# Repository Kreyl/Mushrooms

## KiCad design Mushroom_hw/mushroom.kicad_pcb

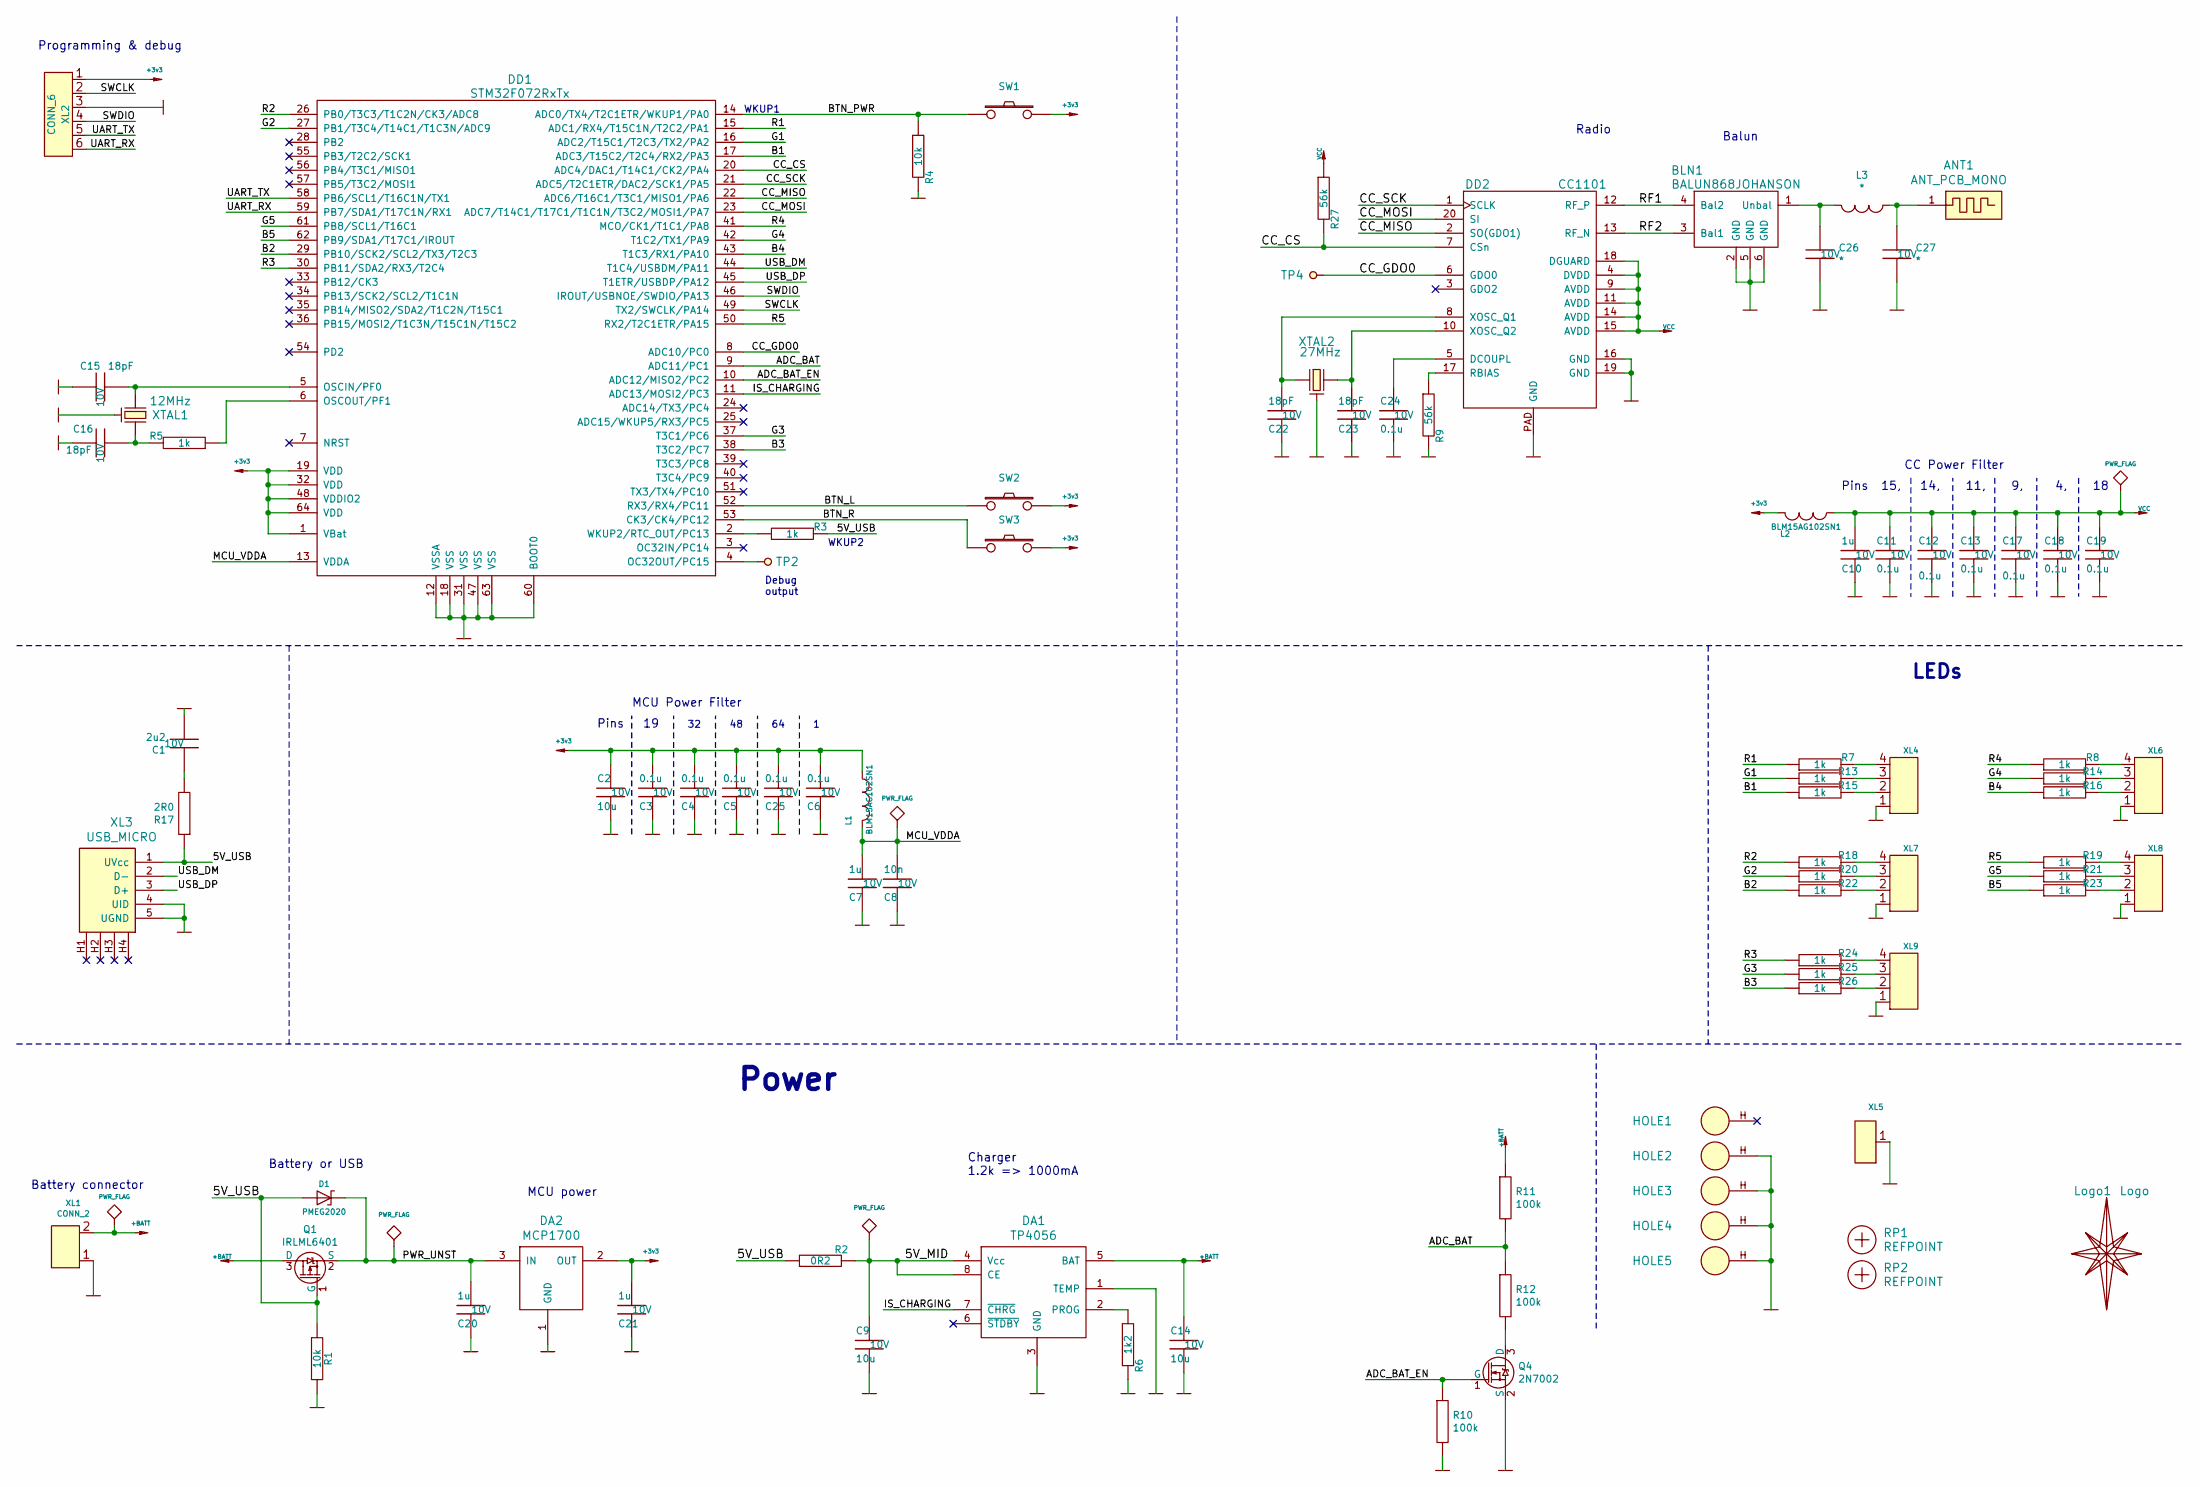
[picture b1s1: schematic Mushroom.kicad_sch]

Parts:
ANT1: ANT_PCB_MONO; Firefly_868
BLN1: BALUN868JOHANSON; BALUN_JOHANSON868
C1: 2u2; CAP_0603_Silks; Tolerance 20%; Voltage 10V
C2, C9, C14: 10u; CAP_0603_Silks; Tolerance 20%; Voltage 10V
C3, C4, C5, C6, C11, C12, C13, C17, C18, C19, C24, C25: 0.1u; CAP_0603_Silks; Tolerance 20%; Voltage 10V
C7, C10, C20, C21: 1u; CAP_0603_Silks; Tolerance 20%; Voltage 10V
C8: 10n; CAP_0603_Silks; Tolerance 20%; Voltage 10V
C15, C16, C22, C23: 18pF; CAP_0603_Silks; Tolerance 20%; Voltage 10V
C26, C27: *; CAP_0402; Tolerance 20%; Voltage 10V
D1: PMEG2020; SOD323
DA1: TP4056; SO8_150MIL
DA2: MCP1700; SOT23-3A
DD1: STM32F072RxTx; LQFP64
DD2: CC1101; QFN20
HOLE1, HOLE2, HOLE3, HOLE4, HOLE5: HOLE_METALLED; Hole2d4_out4d4mm
L1, L2: BLM15AG102SN1; IND_0402; Tolerance 20%
L3: *; IND_0402; Tolerance 20%
Logo1: Logo; Ostranna_16d9_13d5
Q1: IRLML6401; SOT23-3
Q4: 2N7002; SOT23-3
R1, R4: 10k; RES_0603; Tolerance 1%
R2: 0R2; RES_1206; Tolerance 1%
R3, R5, R7, R8, R13, R14, R15, R16, R18, R19, R20, R21, R22, R23, R24, R25, R26: 1k; RES_0603; Tolerance 1%
R6: 1k2; RES_0603; Tolerance 1%
R9, R27: 56k; RES_0603; Tolerance 1%
R10, R11, R12: 100k; RES_0603; Tolerance 1%
R17: 2R0; RES_0603; Tolerance 1%
RP1, RP2: REFPOINT; REF_POINT_1MM
SW1, SW2, SW3: BUTTON; BTN_4x4_SMD
TP2, TP4: TESTPOINT; TESTPOINT_1MM
XL1: CONN_2; SLD_2_2D5
XL2: CONN_6; PLS-6_LOCK
XL3: USB_MICRO; USBmicro_MOLEX_1050170001
XL4, XL6, XL7, XL8, XL9: CONN_4; WB-04(MW-4M)
XL5: CONN_1; PLS-1Square
XTAL1: 12MHz; 03225C4
XTAL2: 27MHz; 03225C4

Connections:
+3v3: C2.2, C3.1, C4.1, C5.1, C6.1, C21.1, C25.1, DA2.2 (OUT), DD1.1 (VBat), DD1.19 (VDD), DD1.32 (VDD), DD1.48 (VDDIO2), DD1.64 (VDD), L1.1, L2.2, SW1.2, SW2.2, SW3.2, XL2.1
+BATT: C14.2, DA1.5 (BAT), Q1.3 (D), R11.1, XL1.2 (PM)
/5V_MID: C9.2, DA1.4 (Vcc), DA1.8 (CE), R2.2
/5V_USB: D1.A, Q1.1 (G), R1.1, R2.1, R3.2, R17.1, XL3.1 (UVcc)
/ADC_BAT: DD1.9 (ADC11/PC1), R11.2, R12.1
/ADC_BAT_EN: DD1.10 (ADC12/MISO2/PC2), Q4.1 (G), R10.1
/B1: DD1.17 (ADC3/T15C2/T2C4/RX2/PA3), R15.1
/B2: DD1.29 (PB10/SCK2/SCL2/TX3/T2C3), R22.1
/B3: DD1.38 (T3C2/PC7), R26.1
/B4: DD1.43 (T1C3/RX1/PA10), R16.1
/B5: DD1.62 (PB9/SDA1/T17C1/IROUT), R23.1
/BTN_L: DD1.52 (RX3/RX4/PC11), SW2.1
/BTN_PWR: DD1.14 (ADC0/TX4/T2C1ETR/WKUP1/PA0), R4.1, SW1.1
/BTN_R: DD1.53 (CK3/CK4/PC12), SW3.1
/CC_CS: DD1.20 (ADC4/DAC1/T14C1/CK2/PA4), DD2.7 (CSn), R27.2
/CC_GDO0: DD1.8 (ADC10/PC0), DD2.6 (GDO0), TP4.1
/CC_MISO: DD1.22 (ADC6/T16C1/T3C1/MISO1/PA6), DD2.2 (SO(GDO1))
/CC_MOSI: DD1.23 (ADC7/T14C1/T17C1/T1C1N/T3C2/MOSI1/PA7), DD2.20 (SI)
/CC_SCK: DD1.21 (ADC5/T2C1ETR/DAC2/SCK1/PA5), DD2.1 (SCLK)
/G1: DD1.16 (ADC2/T15C1/T2C3/TX2/PA2), R13.1
/G2: DD1.27 (PB1/T3C4/T14C1/T1C3N/ADC9), R20.1
/G3: DD1.37 (T3C1/PC6), R25.1
/G4: DD1.42 (T1C2/TX1/PA9), R14.1
/G5: DD1.61 (PB8/SCL1/T16C1), R21.1
/IS_CHARGING: DA1.7 (~CHRG), DD1.11 (ADC13/MOSI2/PC3)
/MCU_VDDA: C7.1, C8.1, DD1.13 (VDDA), L1.2
/PWR_UNST: C20.1, D1.C, DA2.3 (IN), Q1.2 (S)
/R1: DD1.15 (ADC1/RX4/T15C1N/T2C2/PA1), R7.1
/R2: DD1.26 (PB0/T3C3/T1C2N/CK3/ADC8), R18.1
/R3: DD1.30 (PB11/SDA2/RX3/T2C4), R24.1
/R4: DD1.41 (MCO/CK1/T1C1/PA8), R8.1
/R5: DD1.50 (RX2/T2C1ETR/PA15), R19.1
/RF1: BLN1.4 (Bal2), DD2.12 (RF_P)
/RF2: BLN1.3 (Bal1), DD2.13 (RF_N)
/SWCLK: DD1.49 (TX2/SWCLK/PA14), XL2.2
/SWDIO: DD1.46 (IROUT/USBNOE/SWDIO/PA13), XL2.4
/UART_RX: DD1.59 (PB7/SDA1/T17C1N/RX1), XL2.6
/UART_TX: DD1.58 (PB6/SCL1/T16C1N/TX1), XL2.5
/USB_DM: DD1.44 (T1C4/USBDM/PA11), XL3.2 (D-)
/USB_DP: DD1.45 (T1ETR/USBDP/PA12), XL3.3 (D+)
GND: BLN1.2 (GND), BLN1.5 (GND), BLN1.6 (GND), C1.2, C2.1, C3.2, C4.2, C5.2, C6.2, C7.2, C8.2, C9.1, C10.2, C11.2, C12.2, C13.2, C14.1, C15.2, C16.2, C17.2, C18.2, C19.2, C20.2, C21.2, C22.2, C23.2, C24.1, C25.2, C26.2, C27.2, DA1.1 (TEMP), DA1.3 (GND), DA2.1 (GND), DD1.12 (VSSA), DD1.18 (VSS), DD1.31 (VSS), DD1.47 (VSS), DD1.60 (BOOT0), DD1.63 (VSS), DD2.16 (GND), DD2.19 (GND), DD2.PAD (GND), HOLE2.H, HOLE3.H, HOLE4.H, HOLE5.H, Q4.2 (S), R1.2, R4.2, R6.2, R9.2, R10.2, XL1.1, XL2.3, XL3.4 (UID), XL3.5 (UGND), XL4.1, XL5.1, XL6.1, XL7.1, XL8.1, XL9.1, XTAL1.H, XTAL2.H
unnamed: ANT1.1, C27.1, L3.2
unnamed: BLN1.1 (Unbal), C26.1, L3.1
unnamed: C1.1, R17.2
unnamed: C15.1, DD1.5 (OSCIN/PF0), XTAL1.1
unnamed: C16.1, R5.2, XTAL1.2
unnamed: C22.1, DD2.8 (XOSC_Q1), XTAL2.1
unnamed: C23.1, DD2.10 (XOSC_Q2), XTAL2.2
unnamed: C24.2, DD2.5 (DCOUPL)
unnamed: DA1.2 (PROG), R6.1
unnamed: DD1.2 (WKUP2/RTC_OUT/PC13), R3.1
unnamed: DD1.4 (OC32OUT/PC15), TP2.1
unnamed: DD1.6 (OSCOUT/PF1), R5.1
unnamed: DD2.17 (RBIAS), R9.1
unnamed: Q4.3 (D), R12.2
unnamed: R7.2, XL4.4
unnamed: R8.2, XL6.4
unnamed: R13.2, XL4.3
unnamed: R14.2, XL6.3
unnamed: R15.2, XL4.2 (PM)
unnamed: R16.2, XL6.2 (PM)
unnamed: R18.2, XL7.4
unnamed: R19.2, XL8.4
unnamed: R20.2, XL7.3
unnamed: R21.2, XL8.3
unnamed: R22.2, XL7.2 (PM)
unnamed: R23.2, XL8.2 (PM)
unnamed: R24.2, XL9.4
unnamed: R25.2, XL9.3
unnamed: R26.2, XL9.2 (PM)
VCC: C10.1, C11.1, C12.1, C13.1, C17.1, C18.1, C19.1, DD2.4 (DVDD), DD2.9 (AVDD), DD2.11 (AVDD), DD2.14 (AVDD), DD2.15 (AVDD), DD2.18 (DGUARD), L2.1, R27.1

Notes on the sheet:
Battery connector
Programming & debug
Battery or USB
MCU power
Pins
MCU Power Filter
Power
WKUP1
Debug output
WKUP2
Charger 1.2k => 1000mA
Radio
Balun
Pins 15, 14, 11, 9, 4, 18
CC Power Filter
LEDs

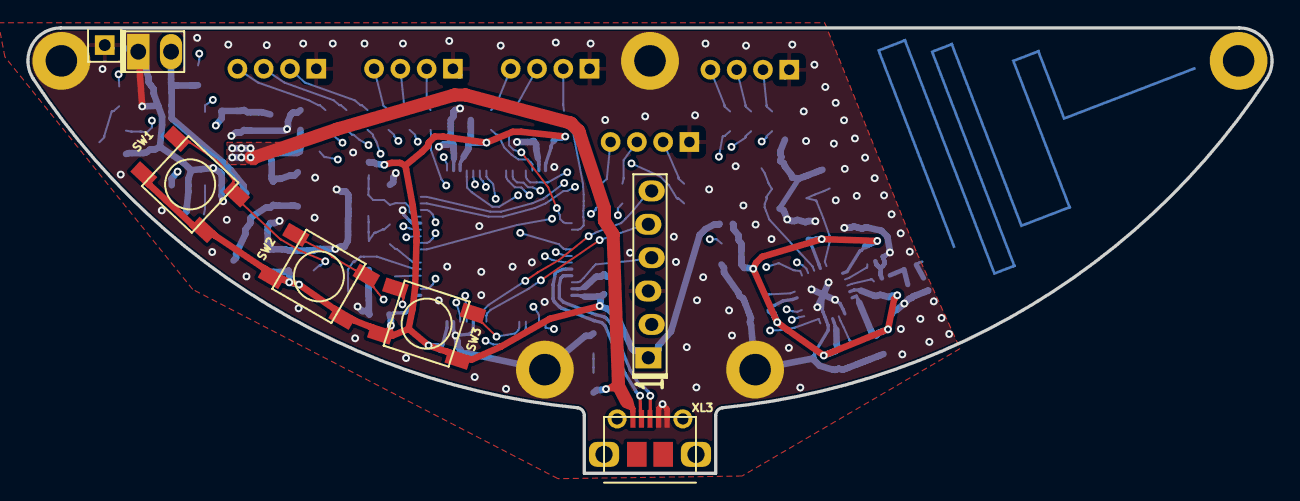
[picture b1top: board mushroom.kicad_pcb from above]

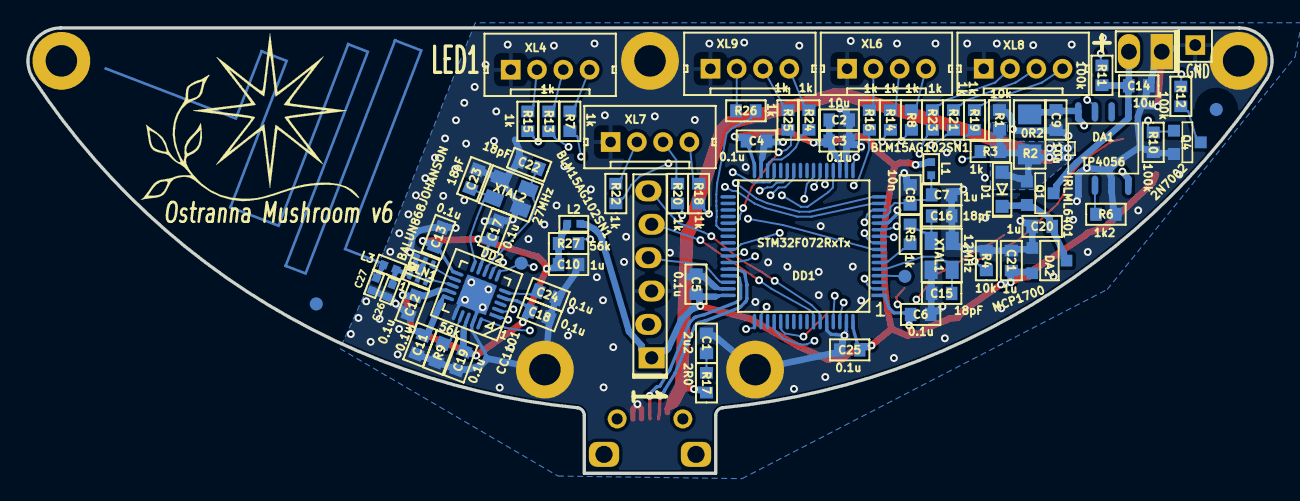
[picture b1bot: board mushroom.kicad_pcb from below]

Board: 4 copper layers, 94.7 x 33.9 mm, 90 parts (80 on the bottom side), 71 nets.

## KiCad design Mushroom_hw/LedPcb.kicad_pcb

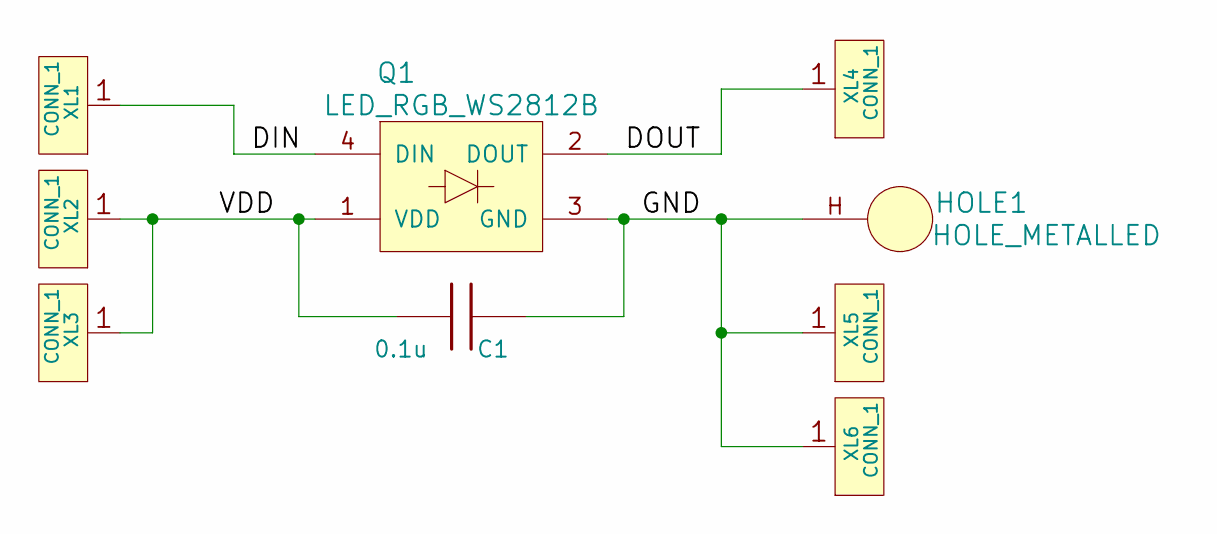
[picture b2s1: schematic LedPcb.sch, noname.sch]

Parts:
C1: 0.1u; CAP_0603
HOLE1: HOLE_METALLED; Hole1d8_out3d2mm
Q1: LED_RGB_WS2812B; LED_WS2812B
XL1, XL2, XL3, XL4, XL5, XL6: CONN_1; Oval3x1.5

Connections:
/DIN: Q1.4 (DIN), XL1.1
/DOUT: Q1.2 (DOUT), XL4.1
/GND: C1.2, HOLE1.H, Q1.3 (GND), XL5.1, XL6.1
/VDD: C1.1, Q1.1 (VDD), XL2.1, XL3.1

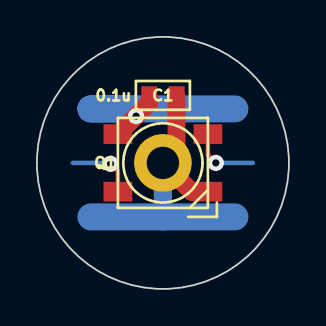
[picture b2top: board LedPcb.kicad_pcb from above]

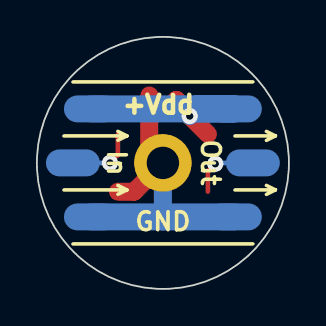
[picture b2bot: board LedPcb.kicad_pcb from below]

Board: 2 copper layers, 14.0 x 14.0 mm, 9 parts (6 on the bottom side), 4 nets.

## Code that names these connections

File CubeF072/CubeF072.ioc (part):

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Mcu.Name=STM32F072R(8-B)Tx
Mcu.Package=LQFP64
Mcu.UserName=STM32F072R8Tx
PA0.Mode=SYS_WakeUp0
PA0.Signal=SYS_WKUP1
PA1.Signal=S_TIM2_CH2
PA10.Signal=S_TIM1_CH3
PA11.Mode=Device
PA11.Signal=USB_DM
PA12.Mode=Device
PA12.Signal=USB_DP
PA13.Mode=Serial_Wire
PA13.Signal=SYS_SWDIO
PA14.Mode=Serial_Wire
PA14.Signal=SYS_SWCLK
PA15.Signal=S_TIM2_CH1_ETR
PA2.Signal=S_TIM15_CH1
PA3.Signal=S_TIM15_CH2
PA4.Signal=GPIO_Output
PA5.Mode=Full_Duplex_Master
PA5.Signal=SPI1_SCK
PA6.Mode=Full_Duplex_Master
PA6.Signal=SPI1_MISO
PA7.Mode=Full_Duplex_Master
PA7.Signal=SPI1_MOSI
PA8.Signal=S_TIM1_CH1
PA9.Signal=S_TIM1_CH2
PB0.Signal=S_TIM3_CH3
PB1.Signal=S_TIM3_CH4
PB10.Signal=S_TIM2_CH3
PB11.Signal=S_TIM2_CH4
PB13.Mode=I2C
PB13.Signal=I2C2_SCL
PB14.Mode=I2C
PB14.Signal=I2C2_SDA
PB6.Mode=Asynchronous
PB6.Signal=USART1_TX
PB7.Mode=Asynchronous
PB7.Signal=USART1_RX
PB8.Signal=S_TIM16_CH1
PB9.Signal=S_TIM17_CH1
PC11.Signal=GPIO_Input
PC12.Signal=GPIO_Input
PC13.Mode=SYS_WakeUp1
PC13.Signal=SYS_WKUP2
PC2.Mode=IN12
PC2.Signal=ADC_IN12
PC6.Signal=S_TIM3_CH1
PC7.Signal=S_TIM3_CH2
PF0-OSC_IN.Mode=HSE-External-Oscillator
PF0-OSC_IN.Signal=RCC_OSC_IN
PF1-OSC_OUT.Mode=HSE-External-Oscillator
PF1-OSC_OUT.Signal=RCC_OSC_OUT
board=custom

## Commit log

2016-02-16 Buttons controlled
2016-02-23 HW v1 for archive purposes
2016-03-24 Clean-up
2016-07-23 seems like release
2017-02-07 * HW v2 in progress
2017-02-08 + Component placement done
2017-02-08 HW2 sent to production
2017-02-24 + Proceeding with fw
2017-02-25 + WS2812 work ok + Color changing mode
2017-06-10 + Antenna matched
2017-07-09 + New LedPcb (WS2812 only)
2017-07-11 + OS works, sleep and UART work, too
2017-07-11 + Buttons work
2017-07-11 + WS2812 work
2017-07-11 Color changes on buttons
2017-07-13 Before switch to bit-by-bit WS2812
2017-07-13 4-bit
2017-07-19 WS2812 modified
2017-07-19 Comment changed
2017-07-19 + sk6812 started
2017-07-19 + 150 sk6812 works
2017-09-29 Release
2017-11-15 + IFA antenna
2017-11-15 Rx done
2017-11-16 TX and RX done
2017-11-30 + PCB v3
2017-11-30 + WS2812 work ok
2017-12-02 + PCB v4
2017-12-02 + Radio seems to work
2017-12-06 + Colindo Board job
2017-12-06 Minor change
2017-12-06 Minor
2017-12-06 Works
2017-12-07 + Save last color to flash
2017-12-29 +v4 without silks, but ready for production
2018-04-15 Smth
2018-04-15 RX ok Proceeding with effects
2018-06-10 + One by one
2018-06-10 Switch to Atollic
2018-07-17 Switching to newer effects class
2018-07-17 Switched to newer effects paradigma
2018-07-17 + pwr pin management RC
2018-08-04 Something
2018-08-05 Proceeding
2018-08-05 - Radio removed
2018-08-05 Save implemented Release
2018-08-05 + Radio init and powered down
2018-09-04 + Sequences
2018-09-05 App name changed
2018-11-08 + HW v5
2018-11-08 Something strange
2018-11-08 Magenta & Yellow
2019-03-02 Switch to v5
2019-03-03 John the mushroomer RC
2019-04-19 Sch fixed
2019-08-12 Simple
2021-05-21 Touch demo works
2021-05-22 + Sch + PCB Sent to factory
2021-05-30 Switch to CubeIDE
